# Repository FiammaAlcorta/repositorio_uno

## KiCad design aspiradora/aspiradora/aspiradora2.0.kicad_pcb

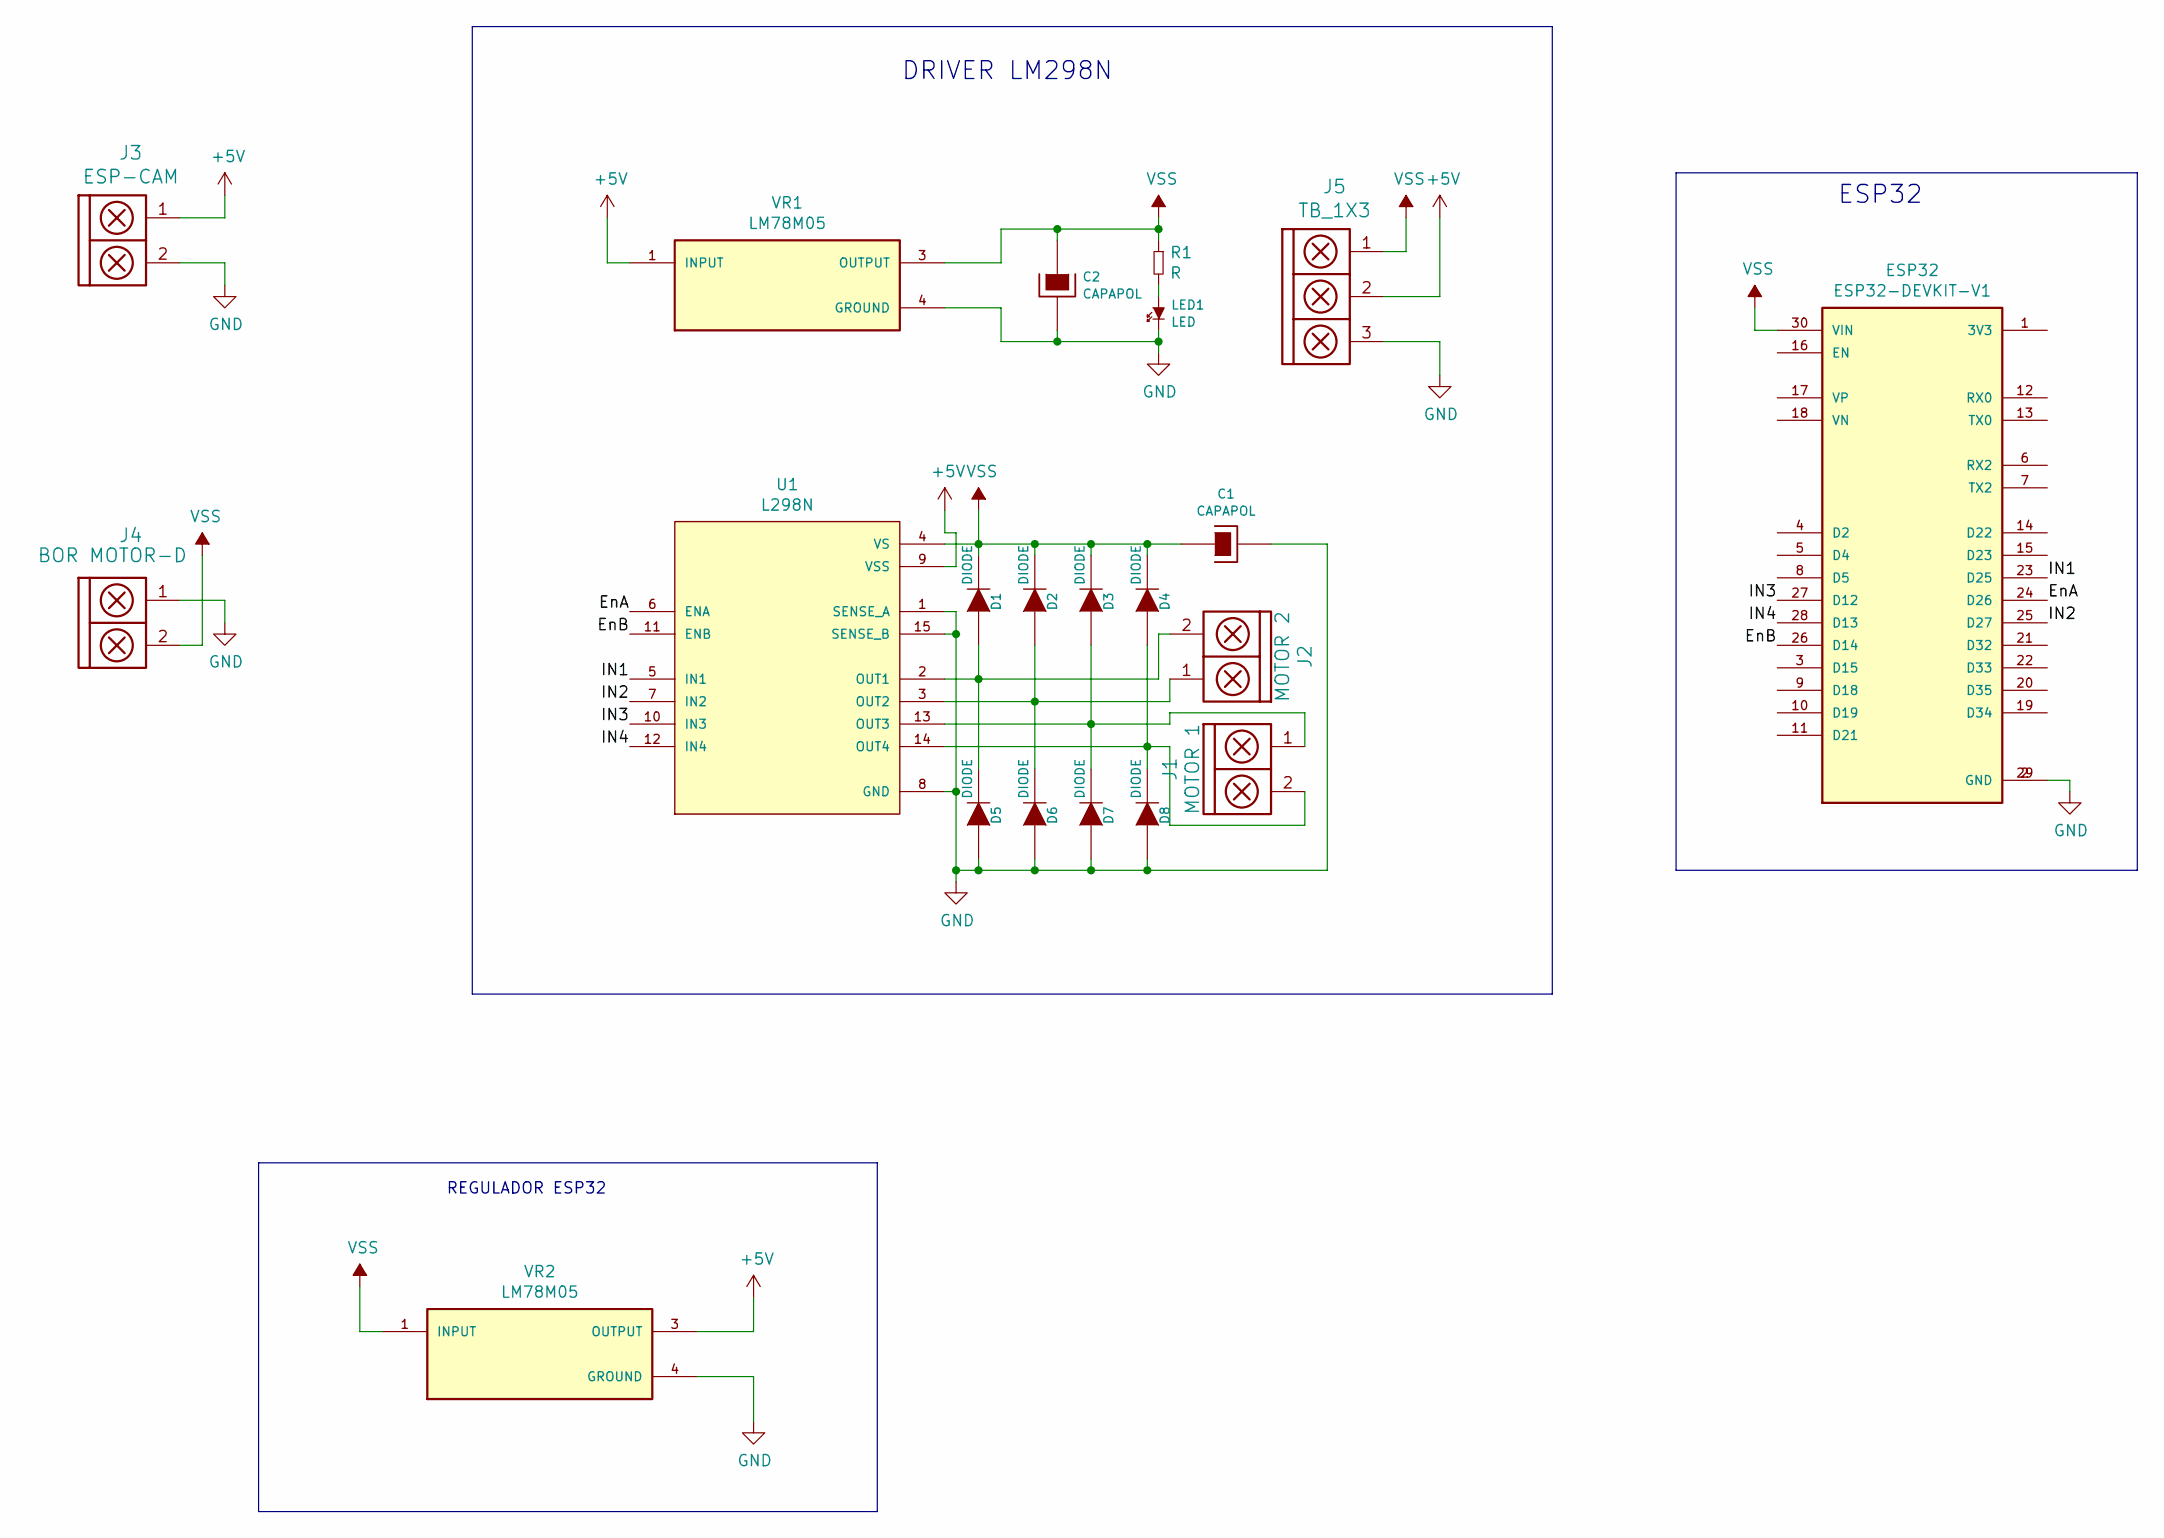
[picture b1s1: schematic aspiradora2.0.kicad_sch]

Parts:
C1, C2: CAPAPOL; CAP_ELEC_5x11mm
D1, D2, D3, D4, D5, D6, D7, D8: DIODE; DO-41
ESP32: ESP32-DEVKIT-V1; MODULE_ESP32_DEVKIT_V1; PARTREV N/A
J1: MOTOR 1; BORNERA2_AZUL
J2: MOTOR 2; BORNERA2_AZUL
J3: ESP-CAM; BORNERA2_AZUL
J4: BOR MOTOR-D; BORNERA2_AZUL
J5: TB_1X3; BORNERA3
LED1: LED; led_3mm_green
R1: R; RES0.3
U1: L298N; TO127P2020X500X2100-15
VR1, VR2: LM78M05; VREG_LM78M05; PARTREV G

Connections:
+5V: J3.1, J5.2, U1.9 (VSS), VR1.1 (INPUT), VR2.3 (OUTPUT)
/EnA: ESP32.24 (D26), U1.6 (ENA)
/EnB: ESP32.26 (D14), U1.11 (ENB)
/IN1: ESP32.23 (D25), U1.5 (IN1)
/IN2: ESP32.25 (D27), U1.7 (IN2)
/IN3: ESP32.27 (D12), U1.10 (IN3)
/IN4: ESP32.28 (D13), U1.12 (IN4)
GND: C1.2, C2.2, D5.1 (A), D6.1 (A), D7.1 (A), D8.1 (A), ESP32.2 (GND), ESP32.29 (GND), J3.2, J4.1, J5.3, LED1.2 (K), U1.1 (SENSE_A), U1.8 (GND), U1.15 (SENSE_B), VR1.4 (GROUND), VR2.4 (GROUND)
unnamed: D1.1 (A), D5.2 (K), J2.2, U1.2 (OUT1)
unnamed: D2.1 (A), D6.2 (K), J2.1, U1.3 (OUT2)
unnamed: D3.1 (A), D7.2 (K), J1.1, U1.13 (OUT3)
unnamed: D4.1 (A), D8.2 (K), J1.2, U1.14 (OUT4)
unnamed: LED1.1 (A), R1.2
VSS: C1.1, C2.1, D1.2 (K), D2.2 (K), D3.2 (K), D4.2 (K), ESP32.30 (VIN), J4.2, J5.1, R1.1, U1.4 (VS), VR1.3 (OUTPUT), VR2.1 (INPUT)

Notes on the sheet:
ESP32
REGULADOR ESP32
DRIVER LM298N

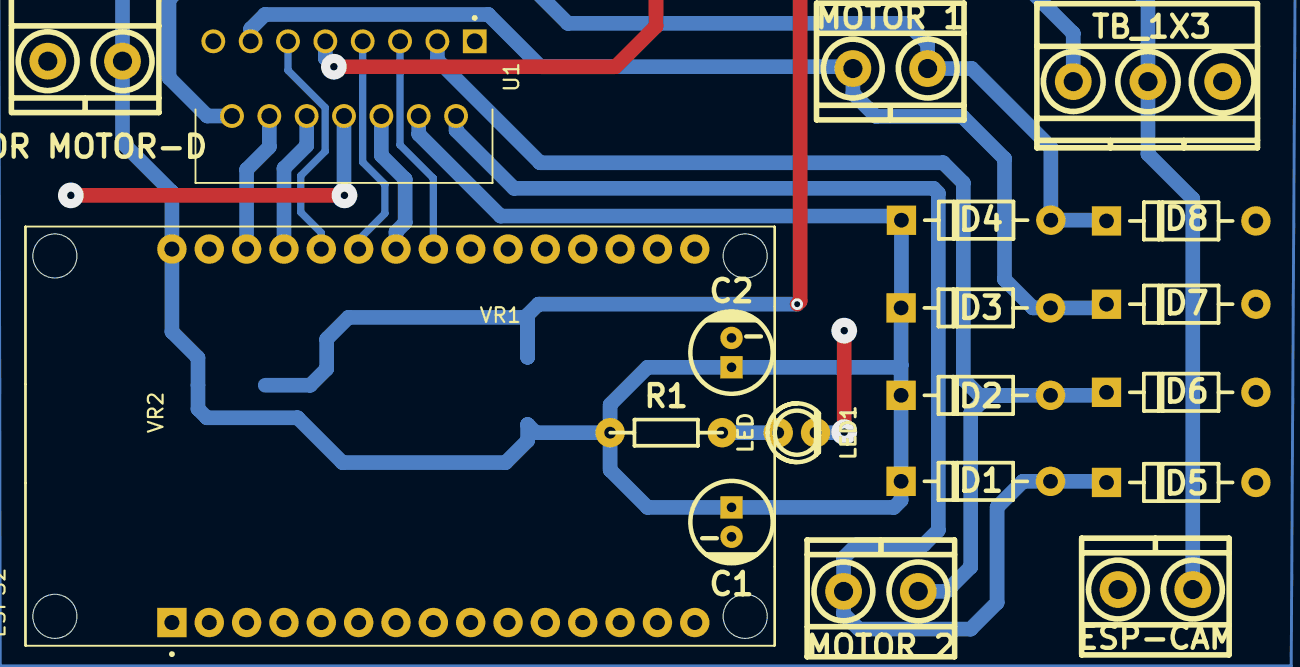
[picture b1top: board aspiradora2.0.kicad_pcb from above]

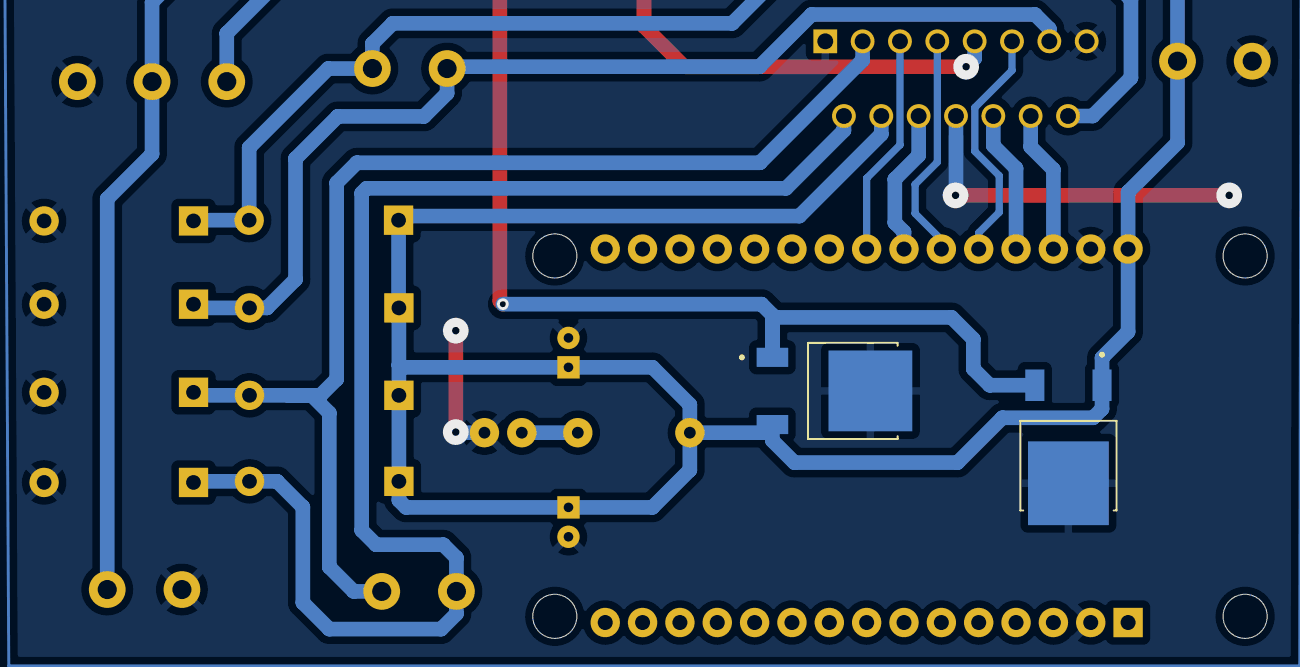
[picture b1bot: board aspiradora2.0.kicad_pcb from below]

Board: 2 copper layers, 21 parts (2 on the bottom side), 14 nets.

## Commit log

2022-08-19 agregue un nuevo archivo
2022-08-19 agregue un nuevo texto
2022-08-28 nuevo texto
2022-12-07 kicad
